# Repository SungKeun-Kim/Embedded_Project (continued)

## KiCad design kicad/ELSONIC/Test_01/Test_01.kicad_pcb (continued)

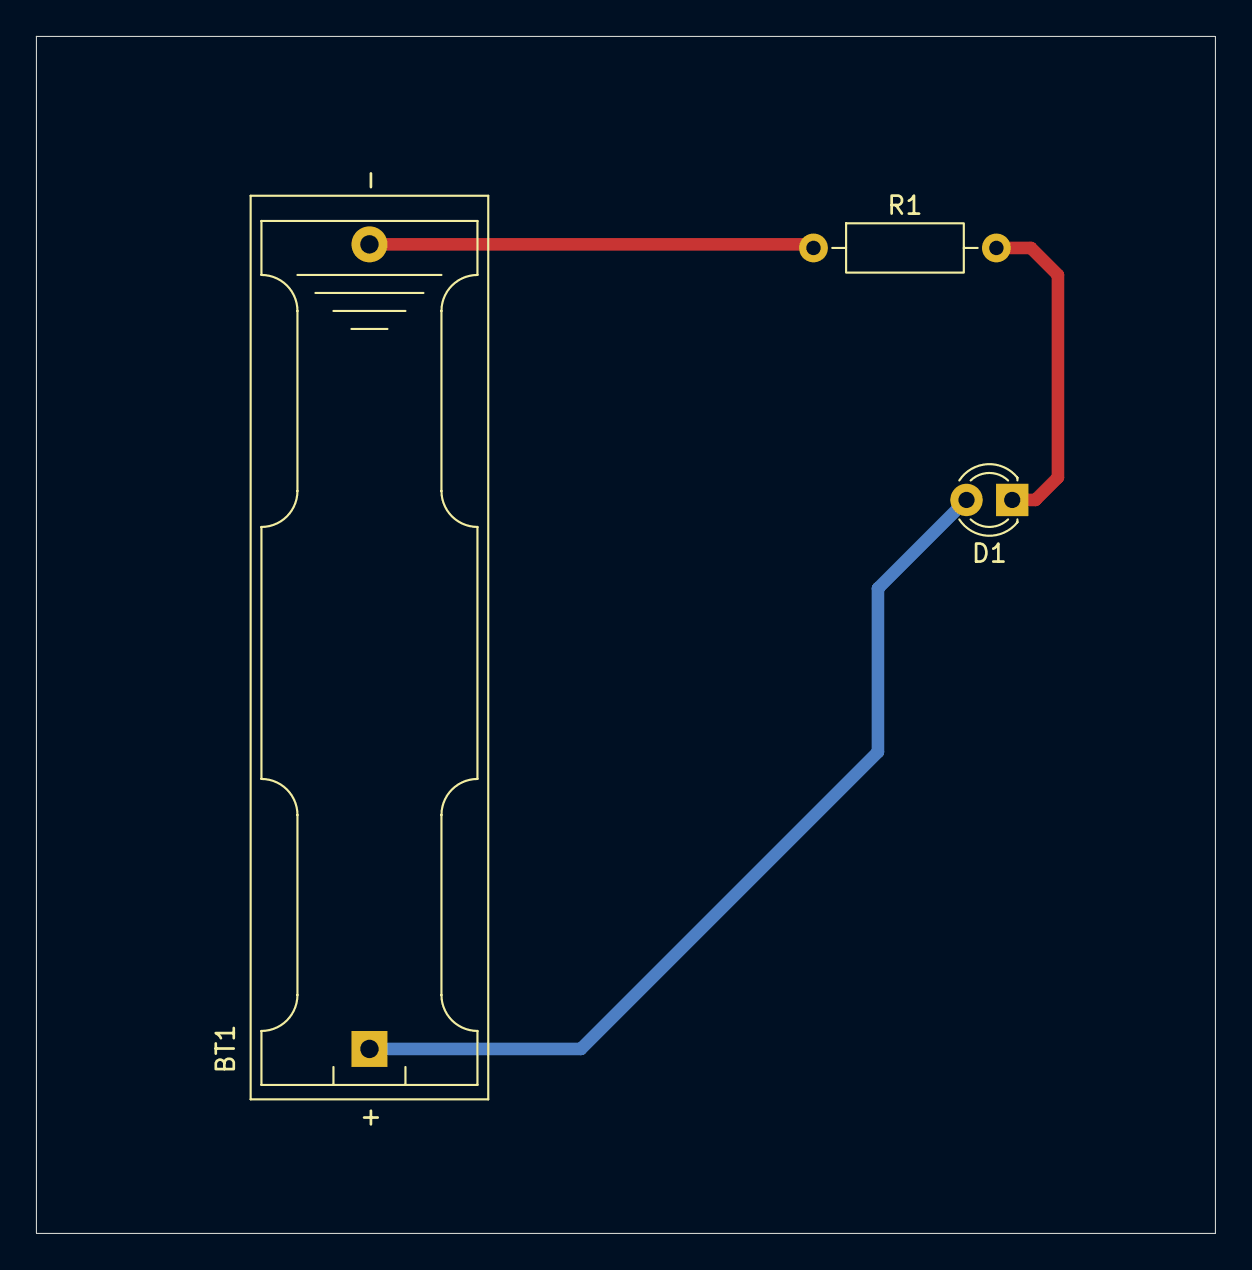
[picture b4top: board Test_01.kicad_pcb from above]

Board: 2 copper layers, 65.5 x 66.5 mm, 3 parts (0 on the bottom side), 3 nets.
